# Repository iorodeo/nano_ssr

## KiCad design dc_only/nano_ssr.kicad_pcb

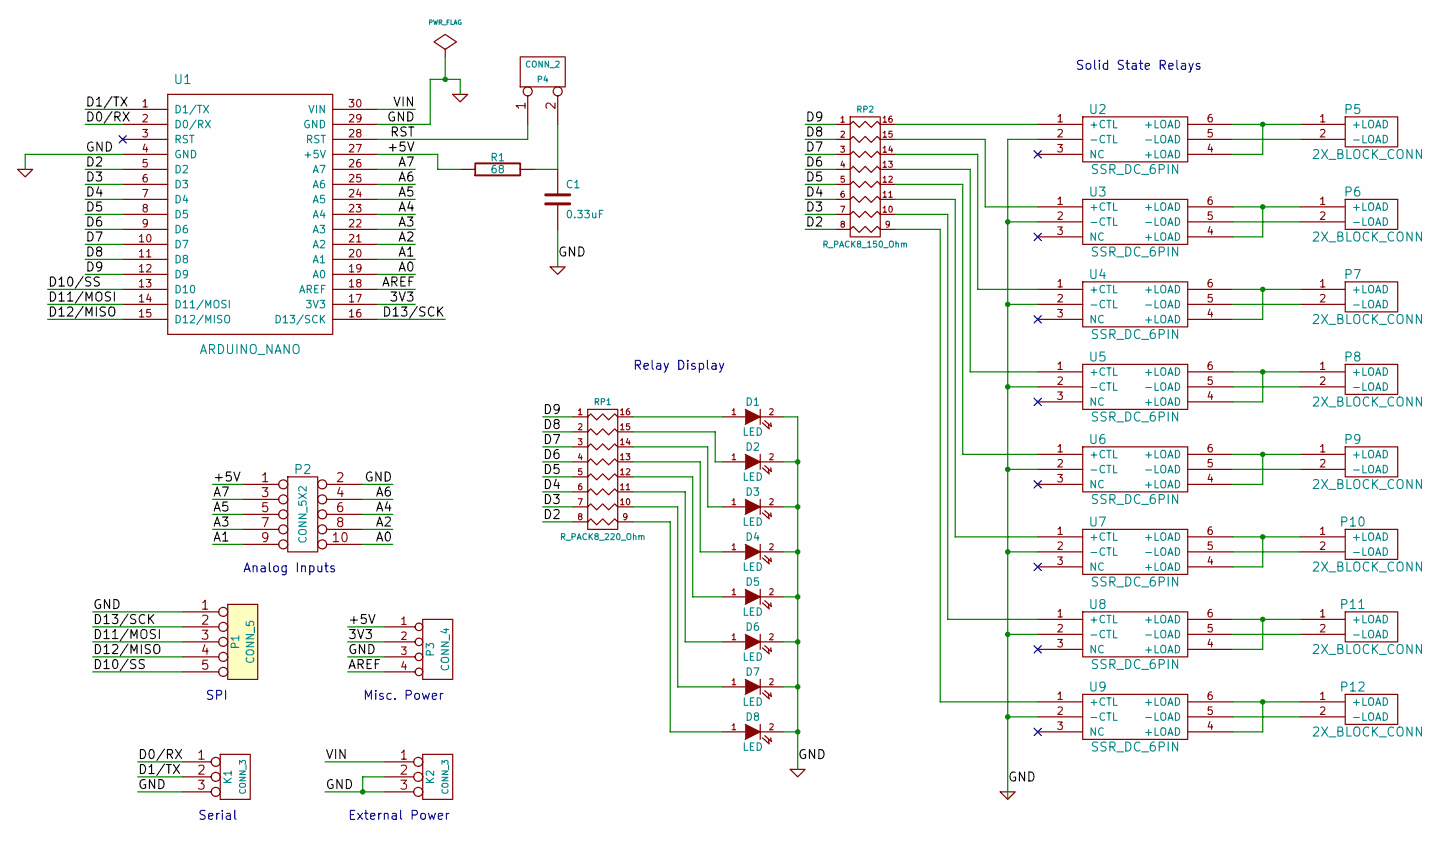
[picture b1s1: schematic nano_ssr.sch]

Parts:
C1: 0.33uF
D1, D2, D3, D4, D5, D6, D7, D8: LED
K1, K2: CONN_3
P1: CONN_5
P2: CONN_5X2
P3: CONN_4
P4: CONN_2
P5, P6, P7, P8, P9, P10, P11, P12: 2X_BLOCK_CONN
R1: 68
RP1: R_PACK8_220_Ohm
RP2: R_PACK8_150_Ohm
U1: ARDUINO_NANO
U2, U3, U4, U5, U6, U7, U8, U9: SSR_DC_6PIN

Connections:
/3V3: P3.2, U1.17 (3V3)
/+5V: P2.1, P3.1, R1.1, U1.27 (+5V)
/A0: P2.10, U1.19 (A0)
/A1: P2.9, U1.20 (A1)
/A2: P2.8, U1.21 (A2)
/A3: P2.7, U1.22 (A3)
/A4: P2.6, U1.23 (A4)
/A5: P2.5, U1.24 (A5)
/A6: P2.4, U1.25 (A6)
/A7: P2.3, U1.26 (A7)
/AREF: P3.4, U1.18 (AREF)
/D0/RX: K1.1, U1.2 (D0/RX)
/D1/TX: K1.2 (PM), U1.1 (D1/TX)
/D2: RP1.8, RP2.8, U1.5 (D2)
/D3: RP1.7, RP2.7, U1.6 (D3)
/D4: RP1.6, RP2.6, U1.7 (D4)
/D5: RP1.5, RP2.5, U1.8 (D5)
/D6: RP1.4, RP2.4, U1.9 (D6)
/D7: RP1.3, RP2.3, U1.10 (D7)
/D8: RP1.2, RP2.2, U1.11 (D8)
/D9: RP1.1, RP2.1, U1.12 (D9)
/D10/SS: P1.5, U1.13 (D10)
/D11/MOSI: P1.3, U1.14 (D11/MOSI)
/D12/MISO: P1.4, U1.15 (D12/MISO)
/D13/SCK: P1.2, U1.16 (D13/SCK)
/GND: C1.2, D1.2 (K), D2.2 (K), D3.2 (K), D4.2 (K), D5.2 (K), D6.2 (K), D7.2 (K), D8.2 (K), K1.3, K2.2 (PM), K2.3, P1.1, P2.2, P3.3, U1.4 (GND), U1.29 (GND), U2.2 (-CTL), U3.2 (-CTL), U4.2 (-CTL), U5.2 (-CTL), U6.2 (-CTL), U7.2 (-CTL), U8.2 (-CTL), U9.2 (-CTL)
/RST: P4.1, U1.28 (RST)
/VIN: K2.1, U1.30 (VIN)
unnamed: P5.2 (-LOAD), U2.5 (-LOAD)
unnamed: C1.1, P4.2 (PM), R1.2
unnamed: P11.1 (+LOAD), U8.4 (+LOAD), U8.6 (+LOAD)
unnamed: P9.1 (+LOAD), U6.4 (+LOAD), U6.6 (+LOAD)
unnamed: P7.1 (+LOAD), U4.4 (+LOAD), U4.6 (+LOAD)
unnamed: P6.1 (+LOAD), U3.4 (+LOAD), U3.6 (+LOAD)
unnamed: D7.1 (A), RP1.10 (R7)
unnamed: D5.1 (A), RP1.12 (R5)
unnamed: D3.1 (A), RP1.14 (R3)
unnamed: D2.1 (A), RP1.15 (R2)
unnamed: P12.1 (+LOAD), U9.4 (+LOAD), U9.6 (+LOAD)
unnamed: P10.1 (+LOAD), U7.4 (+LOAD), U7.6 (+LOAD)
unnamed: P8.1 (+LOAD), U5.4 (+LOAD), U5.6 (+LOAD)
unnamed: P5.1 (+LOAD), U2.4 (+LOAD), U2.6 (+LOAD)
unnamed: RP2.9 (R8), U9.1 (+CTL)
unnamed: RP2.11 (R6), U7.1 (+CTL)
unnamed: RP2.13 (R4), U5.1 (+CTL)
unnamed: RP2.15 (R2), U3.1 (+CTL)
unnamed: RP2.16 (R1), U2.1 (+CTL)
unnamed: RP2.14 (R3), U4.1 (+CTL)
unnamed: RP2.12 (R5), U6.1 (+CTL)
unnamed: RP2.10 (R7), U8.1 (+CTL)
unnamed: D1.1 (A), RP1.16 (R1)
unnamed: D4.1 (A), RP1.13 (R4)
unnamed: D6.1 (A), RP1.11 (R6)
unnamed: D8.1 (A), RP1.9 (R8)
unnamed: P6.2 (-LOAD), U3.5 (-LOAD)
unnamed: P7.2 (-LOAD), U4.5 (-LOAD)
unnamed: P8.2 (-LOAD), U5.5 (-LOAD)
unnamed: P9.2 (-LOAD), U6.5 (-LOAD)
unnamed: P10.2 (-LOAD), U7.5 (-LOAD)
unnamed: P11.2 (-LOAD), U8.5 (-LOAD)
unnamed: P12.2 (-LOAD), U9.5 (-LOAD)

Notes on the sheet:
Solid State Relays
Relay Display
External Power
Serial
Misc. Power
SPI
Analog Inputs

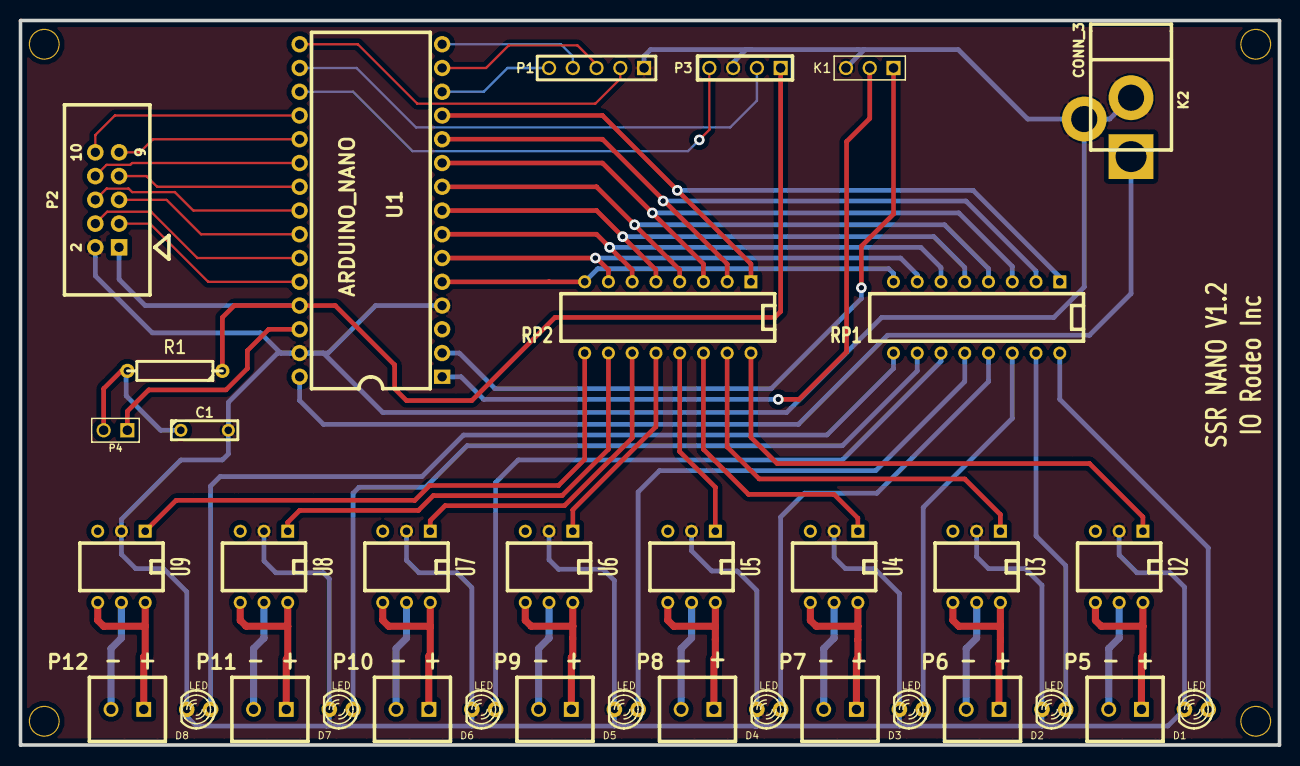
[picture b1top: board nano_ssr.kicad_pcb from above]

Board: 2 copper layers, 134.6 x 77.5 mm, 39 parts (0 on the bottom side), 61 nets.

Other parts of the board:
MOUNT_HOLE: VAL**; MOUNT_HOLE_4_40
MOUNT_HOLE#2, MOUNT_HOLE#3, MOUNT_HOLE#4: VAL**; MOUNT_HOLE_4_40

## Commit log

2010-11-30 Project creation.
2010-11-30 Added creative commons license.
2012-01-05 Modified power jack through hole sizes.
2012-02-14 Modified board and plotted new gerber files v1p1
2012-02-14 Added gerber files for v1p1. Previous hg push did not add these files.
2012-06-04 Modified resistor annotation.
2012-06-04 Added svg of schematic.
2013-06-19 Modified ps and pdf files.
2013-07-06 Moved design to dc_only directory
2013-07-07 Created ac/dc version of the ssr shield for arduino nano.
2013-07-08 Fixed issure with led pads. Added additional anotation to sild screen.
2015-04-07 Created v1.1 and new gerber files for ac_dc version. Modified filled zones slightly - decreased spoke length.
2015-04-23 Added pdf of schematic.
2016-02-01 Modified schematic pdfs.
2016-03-23 Fixed library issue with dc_only version.
2016-07-06 Updated BOM's so that all parts are from digikey (accept for the arduino nano).
2016-07-14 Added zip of v1.1 gerber files.
2017-10-24 Added gerber files for v1.2. Fixed issue with back solder mask.
2017-10-25 Fixed additional issue with missing solder mask for dc version of nano ssr.
2018-03-08 Fixed part name in dc_dc BOM.
2018-03-19 Added link to Arduino and Python libraries on schematic.
